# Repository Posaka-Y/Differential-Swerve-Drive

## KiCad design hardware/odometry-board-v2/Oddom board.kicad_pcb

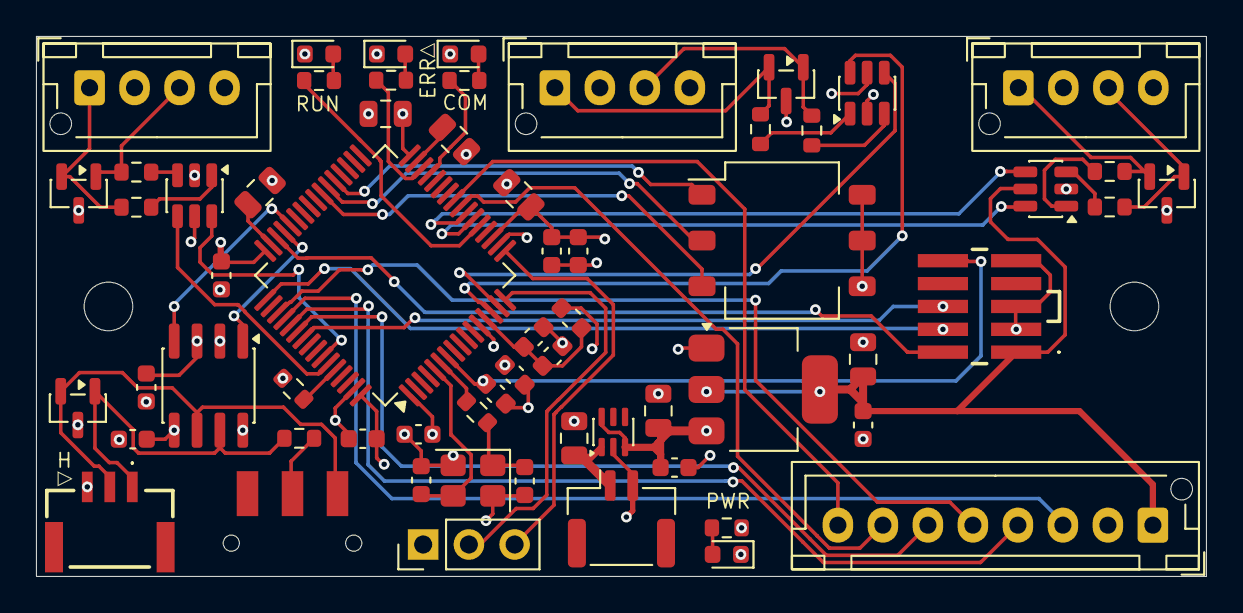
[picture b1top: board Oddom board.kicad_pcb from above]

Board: 4 copper layers, 65.0 x 30.0 mm, 63 parts (0 on the bottom side), 56 nets.

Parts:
C1: 2.2uF; C_0805_2012Metric
C2, C4, C8, C9, C11, C12, C13, C14, C18, C19, C22, C28: 100nF; C_0603_1608Metric
C3, C5: 10uF; C_0805_2012Metric
C6, C7: 10pF; C_0603_1608Metric
C10: 4.7uF; C_0805_2012Metric
C16: 1uF; C_0603_1608Metric
C20, C21, C27: 2.2 µF; C_0805_2012Metric
D1: ESD2CAN24DBZRQ1; SOT-23
D2, D3, D4: D_TVS_Dual_AACESDS452DBZ; SOT-23
D6, D8: LTST-C190KGKT; LED_0603_1608Metric
D9: LTST-C190KSKT; LED_0603_1608Metric
D10: LTST-C190KRKT; LED_0603_1608Metric
FB1: BLM18AG601SN1D; L_0603_1608Metric
J1: SM02B-GHS-TB; JST_GH_SM02B-GHS-TB_1x02-1MP_P1.25mm_Horizontal
J3: FTSH-105-01-L-DV-K-P; FTSH10501LDVKP
J4, J5, J6: Conn_01x04; JST_XH_B4B-XH-AM_1x04_P2.50mm_Vertical
J7: Conn_01x08; JST_XH_B8B-XH-AM_1x08_P2.50mm_Vertical
J8: BM03B-GHS-TBT_LF__SN_; BM03BGHSTBTLFSN
J9: UART_3V3_1x03; PinHeader_1x03_P2.54mm_Vertical
QR*****: git@github.com:Posaka-Y/Differential-Swerve-Drive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; Posaka-Y/Differential-Swerve-Drive.git
R1: 120R; R_0603_1608Metric
R2, R5, R6, R7, R8, R9: 100R; R_0603_1608Metric
R3: RC0603JR-070RL 0R; R_0603_1608Metric
R4: RC0603FR-0710KL 10k; R_0603_1608Metric
R19, R20, R21, R22: 1k; R_0603_1608Metric
SW1: JS102011SAQN
SW3: DS04-254-1-03BK-SMT; SW_DIP_SPSTx03_Slide_Omron_A6S-310x_W8.9mm_P2.54mm
U1: STM32F405RGTx; LQFP-64_10x10mm_P0.5mm
U2: TLV76133DCYR; SOT-223-3_TabPin2
U3, U7, U9: 74LVC2G17; SOT-23-6
U4: TCAN1051VDRQ1; SOIC-8_3.9x4.9mm_P1.27mm
U5: LM66100DCKR; SOT-363_SC-70-6
Y1: FC3BAEBDI8.0-T1; Crystal_SMD_3225-4Pin_3.2x2.5mm

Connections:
/AMT102_input1/W1_A: U1.22 (PA6), U7.6
/AMT102_input1/W1_B: U1.23 (PA7), U7.4
/AMT102_input2/W1_A: U1.58 (PB6), U9.6
/AMT102_input2/W1_B: U1.59 (PB7), U9.4
/AMT102_input/W1_A: U1.14 (PA0), U3.6
/AMT102_input/W1_B: U1.15 (PA1), U3.4
/BOOT0: R4.2, U1.60 (BOOT0)
/CAN_interface/COMM_RX: U1.44 (PA11), U4.4 (RXD)
/CAN_interface/COMM_TX: U1.45 (PA12), U4.1 (TXD)
COMM: R21.1, U1.29 (PB10)
ERR: R22.1, U1.30 (PB11)
GND: C1.2, C2.2, C3.2, C4.2, C5.2, C6.2, C7.2, C8.2, C9.2, C10.1, C11.2, C12.2, C13.2, C14.2, C16.2, C18.2, C19.2, C20.2, C21.2, C22.2, C27.2, C28.1, D1.3 (GND), D2.3 (common), D3.3 (common), D4.3 (common), D6.1 (K), D8.1 (K), D9.1 (K), D10.1 (K), J1.2, J3.3, J3.5, J3.9, J4.4, J5.4, J6.4, J7.2, J8.3, J9.1, R4.1, SW3.4, SW3.5, SW3.6, U1.12 (VSSA), U1.18 (VSS), U1.63 (VSS), U2.1 (GND), U3.2 (GND), U4.2 (GND), U4.8 (S), U5.2 (GND), U7.2 (GND), U9.2 (GND), Y1.2 (G), Y1.4 (G)
IMU_CS_N: J7.6, U1.54 (PD2)
IMU_INT1: J7.7, U1.24 (PC4)
IMU_INT2: J7.8, U1.25 (PC5)
NRST: C22.1, J3.10, U1.7 (NRST)
unnamed: C6.1, R3.2, Y1.1
unnamed: D1.1 (IO_1), J8.1, R1.1, U4.7 (CANH)
unnamed: D1.2 (IO_2), J8.2, SW1.3 (N.O.), U4.6 (CANL)
unnamed: D2.1 (A1), J4.3, R5.1
unnamed: D2.2 (A2), J4.1, R2.1
unnamed: D3.1 (A1), J5.3, R7.1
unnamed: D3.2 (A2), J5.1, R6.1
unnamed: D4.1 (A1), J6.3, R9.1
unnamed: D4.2 (A2), J6.1, R8.1
unnamed: D6.2 (A), R19.2
unnamed: D8.2 (A), R20.2
unnamed: D9.2 (A), R21.2
unnamed: D10.2 (A), R22.2
unnamed: C1.1, J1.1, U5.1 (VIN)
unnamed: J7.3, U1.52 (PC11)
unnamed: J7.4, U1.53 (PC12)
unnamed: J7.5, U1.51 (PC10)
unnamed: R2.2, U3.1
unnamed: R5.2, U3.3
unnamed: R6.2, U7.1
unnamed: R7.2, U7.3
unnamed: R8.2, U9.1
unnamed: R9.2, U9.3
unnamed: R1.2, SW1.2 (COM)
unnamed: SW3.1, U1.37 (PC6)
unnamed: SW3.2, U1.38 (PC7)
unnamed: SW3.3, U1.39 (PC8)
unnamed: C7.1, U1.5 (PH0), Y1.3
unnamed: R3.1, U1.6 (PH1)
unnamed: C20.1, U1.31 (VCAP_1)
unnamed: C21.1, U1.47 (VCAP_2)
unnamed: C14.1, C16.1, FB1.1, U1.13 (VDDA)
PWR_3.3V: C4.1, C5.1, C8.1, C9.1, C10.2, C11.1, C12.1, C13.1, C19.1, C27.1, C28.2, FB1.2, J3.1, J7.1, R19.1, U1.1 (VBAT), U1.19 (VDD), U1.32 (VDD), U1.48 (VDD), U1.64 (VDD), U2.2 (VO), U3.5 (VCC), U4.5 (VIO), U7.5 (VCC), U9.5 (VCC)
PWR_5V: C2.1, C3.1, C18.1, J4.2, J5.2, J6.2, U2.3 (VI), U4.3 (VCC), U5.3 (~CE), U5.6 (VOUT)
RUN: R20.1, U1.21 (PA5)
SWCLK: J3.4, U1.49 (PA14)
SWDIO: J3.2, U1.46 (PA13)
SWO: J3.6, U1.55 (PB3)
USART2_RX: J9.3, U1.17 (PA3)
USART2_TX: J9.2, U1.16 (PA2)
